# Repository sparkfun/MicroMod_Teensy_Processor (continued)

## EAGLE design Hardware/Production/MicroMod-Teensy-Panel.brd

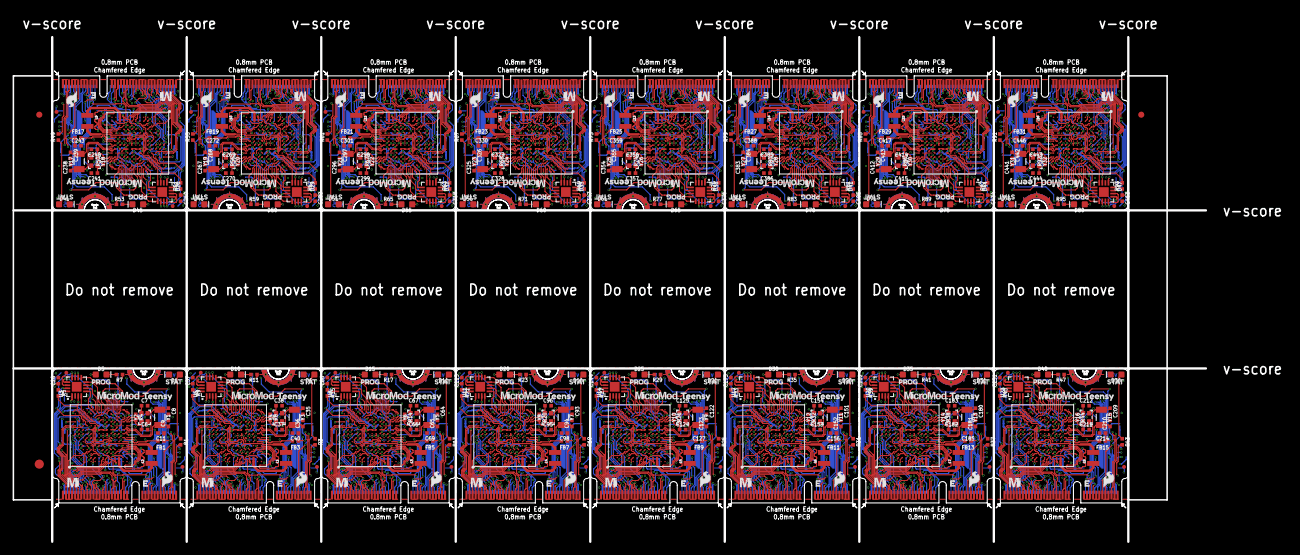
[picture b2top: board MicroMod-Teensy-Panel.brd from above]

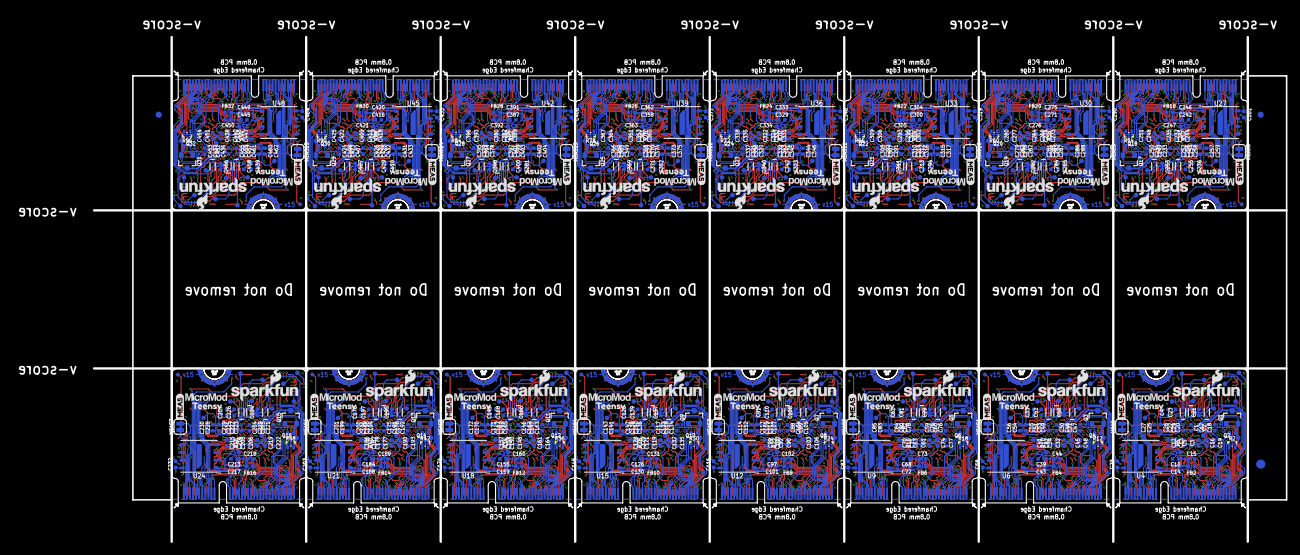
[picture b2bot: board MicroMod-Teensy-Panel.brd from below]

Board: 4 copper layers, 195.0 x 82.5 mm, 1270 parts (835 on the bottom side), 1520 nets.

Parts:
C1, C11, C30, C40, C59, C69, C88, C98, C117, C127, C146, C156, C175, C185, C204, C214, C233, C243, C262, C272, C291, C301, C320, C330, C349, C359, C378, C388, C407, C417, C436, C446: 2.2uF; 0402-TIGHT
C2, C14, C18, C26, C27, C31, C43, C47, C55, C56, C60, C72, C76, C84, C85, C89, C101, C105, C113, C114, C118, C130, C134, C142, C143, C147, C159, C163, C171, C172, C176, C188, C192, C200, C201, C205, C217, C221, C229, C230, C234, C246, C250, C258, C259, C263, C275, C279, C287, C288, C292, C304, C308, C316, C317, C321, C333, C337, C345, C346, C350, C362, C366, C374, C375, C379, C391, C395, C403, C404, C408, C420, C424, C432, C433, C437, C449, C453, C461, C462: 4.7uF; 0402-TIGHT
C3, C4, C12, C13, C15, C17, C20, C22, C23, C24, C25, C28, C29, C32, C33, C41, C42, C44, C46, C49, C51, C52, C53, C54, C57, C58, C61, C62, C70, C71, C73, C75, C78, C80, C81, C82, C83, C86, C87, C90, C91, C99, C100, C102, C104, C107, C109, C110, C111, C112, C115, C116, C119, C120, C128, C129, C131, C133, C136, C138, C139, C140, C141, C144, C145, C148, C149, C157, C158, C160, C162, C165, C167, C168, C169, C170, C173, C174, C177, C178, C186, C187, C189, C191, C194, C196, C197, C198, C199, C202, C203, C206, C207, C215, C216, C218, C220, C223, C225, C226, C227, C228, C231, C232, C235, C236, C244, C245, C247, C249, C252, C254, C255, C256, C257, C260, C261, C264, C265, C273, C274, C276, C278, C281, C283, C284, C285, C286, C289, C290, C293, C294, C302, C303, C305, C307, C310, C312, C313, C314, C315, C318, C319, C322, C323, C331, C332, C334, C336, C339, C341, C342, C343, C344, C347, C348, C351, C352, C360, C361, C363, C365, C368, C370, C371, C372, C373, C376, C377, C380, C381, C389, C390, C392, C394, C397, C399, C400, C401, C402, C405, C406, C409, C410, C418, C419, C421, C423, C426, C428, C429, C430, C431, C434, C435, C438, C439, C447, C448, C450, C452, C455, C457, C458, C459, C460, C463, C464: 0.22uF; 0402-TIGHT
C5, C16, C34, C45, C63, C74, C92, C103, C121, C132, C150, C161, C179, C190, C208, C219, C237, C248, C266, C277, C295, C306, C324, C335, C353, C364, C382, C393, C411, C422, C440, C451: 10nF; 0402-TIGHT
C6, C7, C37, C38, C66, C67, C95, C96, C124, C125, C153, C154, C182, C183, C211, C212, C240, C241, C269, C270, C298, C299, C327, C328, C356, C357, C385, C386, C414, C415, C443, C444: 12pF; 0402-TIGHT
C8, C9, C35, C36, C64, C65, C93, C94, C122, C123, C151, C152, C180, C181, C209, C210, C238, C239, C267, C268, C296, C297, C325, C326, C354, C355, C383, C384, C412, C413, C441, C442: 20pF; 0402-TIGHT
C10, C19, C21, C39, C48, C50, C68, C77, C79, C97, C106, C108, C126, C135, C137, C155, C164, C166, C184, C193, C195, C213, C222, C224, C242, C251, C253, C271, C280, C282, C300, C309, C311, C329, C338, C340, C358, C367, C369, C387, C396, C398, C416, C425, C427, C445, C454, C456: 10uF; 0402-TIGHT
D1, D6, D11, D16, D21, D26, D31, D36, D41, D46, D51, D56, D61, D66, D71, D76: BLUE; LED-0603
D2, D3, D4, D7, D8, D9, D12, D13, D14, D17, D18, D19, D22, D23, D24, D27, D28, D29, D32, D33, D34, D37, D38, D39, D42, D43, D44, D47, D48, D49, D52, D53, D54, D57, D58, D59, D62, D63, D64, D67, D68, D69, D72, D73, D74, D77, D78, D79: 120mA/40V/370mV; SOD-523
D5, D10, D15, D20, D25, D30, D35, D40, D45, D50, D55, D60, D65, D70, D75, D80: Yellow; LED-0603
E$1, E$2, E$3, E$4: FIDUCIAL-1X2
E$5, E$6: FIDUCIAL-1.5X3
FB1, FB2, FB3, FB4, FB5, FB6, FB7, FB8, FB9, FB10, FB11, FB12, FB13, FB14, FB15, FB16, FB17, FB18, FB19, FB20, FB21, FB22, FB23, FB24, FB25, FB26, FB27, FB28, FB29, FB30, FB31, FB32: 120Ω; 0402-TIGHT
FD1, FD2, FD3, FD4, FD5, FD6, FD7, FD8, FD9, FD10, FD11, FD12, FD13, FD14, FD15, FD16, FD17, FD18, FD19, FD20, FD21, FD22, FD23, FD24, FD25, FD26, FD27, FD28, FD29, FD30, FD31, FD32, FD33, FD34, FD35, FD36, FD37, FD38, FD39, FD40, FD41, FD42, FD43, FD44, FD45, FD46, FD47, FD48, FD49, FD50, FD51, FD52, FD53, FD54, FD55, FD56, FD57, FD58, FD59, FD60, FD61, FD62, FD63, FD64: FIDUCIALUFIDUCIAL; FIDUCIAL-MICRO
J1, J2, J3, J4, J5, J6, J7, J8, J9, J10, J11, J12, J13, J14, J15, J16: MICROMOD-2222; M.2-CARD-E-22
L1, L2, L3, L4, L5, L6, L7, L8, L9, L10, L11, L12, L13, L14, L15, L16: 4.7μH; 1008(2520)
LOGO1, LOGO2, LOGO3, LOGO4, LOGO5, LOGO6, LOGO7, LOGO8, LOGO9, LOGO10, LOGO11, LOGO12, LOGO13, LOGO14, LOGO15, LOGO16: SFE_LOGO_NAME_FLAME.1_INCH; SFE_LOGO_NAME_FLAME_.1
MEAS, MEAS1, MEAS2, MEAS3, MEAS4, MEAS5, MEAS6, MEAS7, MEAS8, MEAS9, MEAS10, MEAS11, MEAS12, MEAS13, MEAS14, MEAS15: SMT-JUMPER_2_NC_TRACE_SILK
Q1, Q3, Q5, Q7, Q9, Q11, Q13, Q15, Q17, Q19, Q21, Q23, Q25, Q27, Q29, Q31: 20V/4.2A/52mΩ/1.4W; SOT23-3
Q2, Q4, Q6, Q8, Q10, Q12, Q14, Q16, Q18, Q20, Q22, Q24, Q26, Q28, Q30, Q32: 20V/0.2A/8MHz/1.2Ω/1Vth; SOT-416FL
R1, R3, R7, R11, R13, R17, R19, R23, R25, R29, R31, R35, R37, R41, R43, R47, R49, R53, R55, R59, R61, R65, R67, R71, R73, R77, R79, R83, R85, R89, R91, R95: 1k; 0402-TIGHT
R2, R5, R6, R9, R10, R12, R15, R16, R18, R21, R22, R24, R27, R28, R30, R33, R34, R36, R39, R40, R42, R45, R46, R48, R51, R52, R54, R57, R58, R60, R63, R64, R66, R69, R70, R72, R75, R76, R78, R81, R82, R84, R87, R88, R90, R93, R94, R96: 100k; 0402-TIGHT
R4, R8, R14, R20, R26, R32, R38, R44, R50, R56, R62, R68, R74, R80, R86, R92: 2.2M; 0402-TIGHT
TP1, TP2, TP3, TP4, TP5, TP6, TP7, TP8, TP9, TP10, TP11, TP12, TP13, TP14, TP15, TP16, TP17, TP18, TP19, TP20, TP21, TP22, TP23, TP24, TP25, TP26, TP27, TP28, TP29, TP30, TP31, TP32, TP33, TP34, TP35, TP36, TP37, TP38, TP39, TP40, TP41, TP42, TP43, TP44, TP45, TP46, TP47, TP48, TP49, TP50, TP51, TP52, TP53, TP54, TP55, TP56, TP57, TP58, TP59, TP60, TP61, TP62, TP63, TP64, TP65, TP66, TP67, TP68, TP69, TP70, TP71, TP72, TP73, TP74, TP75, TP76, TP77, TP78, TP79, TP80, TP81, TP82, TP83, TP84, TP85, TP86, TP87, TP88, TP89, TP90, TP91, TP92, TP93, TP94, TP95, TP96, TP97, TP98, TP99, TP100, TP101, TP102, TP103, TP104, TP105, TP106, TP107, TP108, TP109, TP110, TP111, TP112, TP113, TP114, TP115, TP116, TP117, TP118, TP119, TP120, TP121, TP122, TP123, TP124, TP125, TP126, TP127, TP128, TP129, TP130, TP131, TP132, TP133, TP134, TP135, TP136, TP137, TP138, TP139, TP140, TP141, TP142, TP143, TP144, TP145, TP146, TP147, TP148, TP149, TP150, TP151, TP152, TP153, TP154, TP155, TP156, TP157, TP158, TP159, TP160, TP161, TP162, TP163, TP164, TP165, TP166, TP167, TP168, TP169, TP170, TP171, TP172, TP173, TP174, TP175, TP176, TP177, TP178, TP179, TP180, TP181, TP182, TP183, TP184, TP185, TP186, TP187, TP188, TP189, TP190, TP191, TP192, TP193, TP194, TP195, TP196, TP197, TP198, TP199, TP200, TP201, TP202, TP203, TP204, TP205, TP206, TP207, TP208: PAD.03X.03
U1, U2, U7, U10, U13, U16, U19, U22, U25, U28, U31, U34, U37, U40, U43, U46: IMXRT1062DV10X10; IMXRT1062
U3, U5, U8, U11, U14, U17, U20, U23, U26, U29, U32, U35, U38, U41, U44, U47: MKL02Z32VFG4; QFN-16
U4, U6, U9, U12, U15, U18, U21, U24, U27, U30, U33, U36, U39, U42, U45, U48: W25QXX128MBIT-6X5; WSON-8-6X5-SKINNY_CENTERPAD
U$1, U$2, U$3, U$5, U$19, U$20, U$28, U$29, U$37, U$38, U$46, U$47, U$55, U$56, U$64, U$65, U$73, U$74, U$82, U$83, U$91, U$92, U$100, U$101, U$109, U$110, U$118, U$119, U$127, U$128, U$136, U$137: TEENSY2
U$4, U$15, U$24, U$33, U$42, U$51, U$60, U$69, U$78, U$87, U$96, U$105, U$114, U$123, U$132, U$141: MICROMOD_MI_LOGO_.35
U$6, U$16, U$25, U$34, U$43, U$52, U$61, U$70, U$79, U$88, U$97, U$106, U$115, U$124, U$133, U$142: SFE_LOGO_FLAME_.1
U$7, U$11, U$17, U$18, U$26, U$27, U$35, U$36, U$44, U$45, U$53, U$54, U$62, U$63, U$71, U$72, U$80, U$81, U$89, U$90, U$98, U$99, U$107, U$108, U$116, U$117, U$125, U$126, U$134, U$135, U$143, U$144: MICROMOD_LOGO_.3
U$8, U$12, U$21, U$30, U$39, U$48, U$57, U$66, U$75, U$84, U$93, U$102, U$111, U$120, U$129, U$138: MEAS2
U$9, U$13, U$22, U$31, U$40, U$49, U$58, U$67, U$76, U$85, U$94, U$103, U$112, U$121, U$130, U$139: PROG0
U$10, U$14, U$23, U$32, U$41, U$50, U$59, U$68, U$77, U$86, U$95, U$104, U$113, U$122, U$131, U$140: STAT1
Y1, Y3, Y5, Y7, Y9, Y11, Y13, Y15, Y17, Y19, Y21, Y23, Y25, Y27, Y29, Y31: 32.768kHz; CRYSTAL-SMD-3.2X1.5MM
Y2, Y4, Y6, Y8, Y10, Y12, Y14, Y16, Y18, Y20, Y22, Y24, Y26, Y28, Y30, Y32: 24MHz; CRYSTAL-SMD-2.0X1.6MM

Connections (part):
3.3V: D2.A, J1.2, J1.74, Q1.2, R2.1, TP13.P$1
3.3V1: D7.A, J2.2, J2.74, Q3.2, R12.1, TP26.P$1
3.3V2: D12.A, J3.2, J3.74, Q5.2, R18.1, TP39.P$1
3.3V3: D17.A, J4.2, J4.74, Q7.2, R24.1, TP52.P$1
3.3V4: D22.A, J5.2, J5.74, Q9.2, R30.1, TP65.P$1
3.3V5: D27.A, J6.2, J6.74, Q11.2, R36.1, TP78.P$1
3.3V6: D32.A, J7.2, J7.74, Q13.2, R42.1, TP91.P$1
3.3V7: D37.A, J8.2, J8.74, Q15.2, R48.1, TP104.P$1
3.3V8: D42.A, J9.2, J9.74, Q17.2, R54.1, TP117.P$1
3.3V9: D47.A, J10.2, J10.74, Q19.2, R60.1, TP130.P$1
3.3V10: D52.A, J11.2, J11.74, Q21.2, R66.1, TP143.P$1
3.3V11: D57.A, J12.2, J12.74, Q23.2, R72.1, TP156.P$1
3.3V12: D62.A, J13.2, J13.74, Q25.2, R78.1, TP169.P$1
3.3V13: D67.A, J14.2, J14.74, Q27.2, R84.1, TP182.P$1
3.3V14: D72.A, J15.2, J15.74, Q29.2, R90.1, TP195.P$1
3.3V15: D77.A, J16.2, J16.74, Q31.2, R96.1, TP208.P$1
3.3V_CONTROLLED: C1.1, C2.1, C3.1, C4.1, C5.1, C28.1, C29.1, D5.A, FB2.1, Q1.3, R6.1, TP12.P$1, U1.E6, U1.E9, U1.F5, U1.F10, U1.J6, U1.J10, U1.K4, U1.K5, U1.N14, U1.P12, U3.1, U4.8
3.3V_CONTROLLED1: C30.1, C31.1, C32.1, C33.1, C34.1, C57.1, C58.1, D10.A, FB4.1, Q3.3, R10.1, TP25.P$1, U2.E6, U2.E9, U2.F5, U2.F10, U2.J6, U2.J10, U2.K4, U2.K5, U2.N14, U2.P12, U5.1, U6.8
3.3V_CONTROLLED2: C59.1, C60.1, C61.1, C62.1, C63.1, C86.1, C87.1, D15.A, FB6.1, Q5.3, R16.1, TP38.P$1, U7.E6, U7.E9, U7.F5, U7.F10, U7.J6, U7.J10, U7.K4, U7.K5, U7.N14, U7.P12, U8.1, U9.8
3.3V_CONTROLLED3: C88.1, C89.1, C90.1, C91.1, C92.1, C115.1, C116.1, D20.A, FB8.1, Q7.3, R22.1, TP51.P$1, U10.E6, U10.E9, U10.F5, U10.F10, U10.J6, U10.J10, U10.K4, U10.K5, U10.N14, U10.P12, U11.1, U12.8
3.3V_CONTROLLED4: C117.1, C118.1, C119.1, C120.1, C121.1, C144.1, C145.1, D25.A, FB10.1, Q9.3, R28.1, TP64.P$1, U13.E6, U13.E9, U13.F5, U13.F10, U13.J6, U13.J10, U13.K4, U13.K5, U13.N14, U13.P12, U14.1, U15.8
3.3V_CONTROLLED5: C146.1, C147.1, C148.1, C149.1, C150.1, C173.1, C174.1, D30.A, FB12.1, Q11.3, R34.1, TP77.P$1, U16.E6, U16.E9, U16.F5, U16.F10, U16.J6, U16.J10, U16.K4, U16.K5, U16.N14, U16.P12, U17.1, U18.8
3.3V_CONTROLLED6: C175.1, C176.1, C177.1, C178.1, C179.1, C202.1, C203.1, D35.A, FB14.1, Q13.3, R40.1, TP90.P$1, U19.E6, U19.E9, U19.F5, U19.F10, U19.J6, U19.J10, U19.K4, U19.K5, U19.N14, U19.P12, U20.1, U21.8
3.3V_CONTROLLED7: C204.1, C205.1, C206.1, C207.1, C208.1, C231.1, C232.1, D40.A, FB16.1, Q15.3, R46.1, TP103.P$1, U22.E6, U22.E9, U22.F5, U22.F10, U22.J6, U22.J10, U22.K4, U22.K5, U22.N14, U22.P12, U23.1, U24.8
3.3V_CONTROLLED8: C233.1, C234.1, C235.1, C236.1, C237.1, C260.1, C261.1, D45.A, FB18.1, Q17.3, R52.1, TP116.P$1, U25.E6, U25.E9, U25.F5, U25.F10, U25.J6, U25.J10, U25.K4, U25.K5, U25.N14, U25.P12, U26.1, U27.8
3.3V_CONTROLLED9: C262.1, C263.1, C264.1, C265.1, C266.1, C289.1, C290.1, D50.A, FB20.1, Q19.3, R58.1, TP129.P$1, U28.E6, U28.E9, U28.F5, U28.F10, U28.J6, U28.J10, U28.K4, U28.K5, U28.N14, U28.P12, U29.1, U30.8
3.3V_CONTROLLED10: C291.1, C292.1, C293.1, C294.1, C295.1, C318.1, C319.1, D55.A, FB22.1, Q21.3, R64.1, TP142.P$1, U31.E6, U31.E9, U31.F5, U31.F10, U31.J6, U31.J10, U31.K4, U31.K5, U31.N14, U31.P12, U32.1, U33.8
3.3V_CONTROLLED11: C320.1, C321.1, C322.1, C323.1, C324.1, C347.1, C348.1, D60.A, FB24.1, Q23.3, R70.1, TP155.P$1, U34.E6, U34.E9, U34.F5, U34.F10, U34.J6, U34.J10, U34.K4, U34.K5, U34.N14, U34.P12, U35.1, U36.8
3.3V_CONTROLLED12: C349.1, C350.1, C351.1, C352.1, C353.1, C376.1, C377.1, D65.A, FB26.1, Q25.3, R76.1, TP168.P$1, U37.E6, U37.E9, U37.F5, U37.F10, U37.J6, U37.J10, U37.K4, U37.K5, U37.N14, U37.P12, U38.1, U39.8
3.3V_CONTROLLED13: C378.1, C379.1, C380.1, C381.1, C382.1, C405.1, C406.1, D70.A, FB28.1, Q27.3, R82.1, TP181.P$1, U40.E6, U40.E9, U40.F5, U40.F10, U40.J6, U40.J10, U40.K4, U40.K5, U40.N14, U40.P12, U41.1, U42.8
3.3V_CONTROLLED14: C407.1, C408.1, C409.1, C410.1, C411.1, C434.1, C435.1, D75.A, FB30.1, Q29.3, R88.1, TP194.P$1, U43.E6, U43.E9, U43.F5, U43.F10, U43.J6, U43.J10, U43.K4, U43.K5, U43.N14, U43.P12, U44.1, U45.8
3.3V_CONTROLLED15: C436.1, C437.1, C438.1, C439.1, C440.1, C463.1, C464.1, D80.A, FB32.1, Q31.3, R94.1, TP207.P$1, U46.E6, U46.E9, U46.F5, U46.F10, U46.J6, U46.J10, U46.K4, U46.K5, U46.N14, U46.P12, U47.1, U48.8
24MHZ_1: C7.1, U1.N11, Y2.3
24MHZ_2: C6.1, R4.2, U1.P11, Y2.1
24MHZ_3: C38.1, U2.N11, Y4.3
24MHZ_4: C37.1, R8.2, U2.P11, Y4.1
24MHZ_5: C67.1, U7.N11, Y6.3
24MHZ_6: C66.1, R14.2, U7.P11, Y6.1
24MHZ_7: C96.1, U10.N11, Y8.3
24MHZ_8: C95.1, R20.2, U10.P11, Y8.1
24MHZ_9: C125.1, U13.N11, Y10.3
24MHZ_10: C124.1, R26.2, U13.P11, Y10.1
24MHZ_11: C154.1, U16.N11, Y12.3
24MHZ_12: C153.1, R32.2, U16.P11, Y12.1
24MHZ_13: C183.1, U19.N11, Y14.3
24MHZ_14: C182.1, R38.2, U19.P11, Y14.1
24MHZ_15: C212.1, U22.N11, Y16.3
24MHZ_16: C211.1, R44.2, U22.P11, Y16.1
24MHZ_17: C241.1, U25.N11, Y18.3
24MHZ_18: C240.1, R50.2, U25.P11, Y18.1
24MHZ_19: C270.1, U28.N11, Y20.3
24MHZ_20: C269.1, R56.2, U28.P11, Y20.1
24MHZ_21: C299.1, U31.N11, Y22.3
24MHZ_22: C298.1, R62.2, U31.P11, Y22.1
24MHZ_23: C328.1, U34.N11, Y24.3
24MHZ_24: C327.1, R68.2, U34.P11, Y24.1
24MHZ_25: C357.1, U37.N11, Y26.3
24MHZ_26: C356.1, R74.2, U37.P11, Y26.1
24MHZ_27: C386.1, U40.N11, Y28.3
24MHZ_28: C385.1, R80.2, U40.P11, Y28.1
24MHZ_29: C415.1, U43.N11, Y30.3
24MHZ_30: C414.1, R86.2, U43.P11, Y30.1
24MHZ_31: C444.1, U46.N11, Y32.3
24MHZ_32: C443.1, R92.2, U46.P11, Y32.1
32KHZ_1: C8.1, U1.N9, Y1.P$1
32KHZ_2: C9.1, U1.P9, Y1.P$2
32KHZ_3: C36.1, U2.P9, Y3.P$2
32KHZ_4: C35.1, U2.N9, Y3.P$1
32KHZ_5: C65.1, U7.P9, Y5.P$2
32KHZ_6: C64.1, U7.N9, Y5.P$1
32KHZ_7: C94.1, U10.P9, Y7.P$2
32KHZ_8: C93.1, U10.N9, Y7.P$1
32KHZ_9: C123.1, U13.P9, Y9.P$2
32KHZ_10: C122.1, U13.N9, Y9.P$1
32KHZ_11: C152.1, U16.P9, Y11.P$2
32KHZ_12: C151.1, U16.N9, Y11.P$1
32KHZ_13: C181.1, U19.P9, Y13.P$2
32KHZ_14: C180.1, U19.N9, Y13.P$1
32KHZ_15: C210.1, U22.P9, Y15.P$2
32KHZ_16: C209.1, U22.N9, Y15.P$1
32KHZ_17: C239.1, U25.P9, Y17.P$2
32KHZ_18: C238.1, U25.N9, Y17.P$1
32KHZ_19: C268.1, U28.P9, Y19.P$2
32KHZ_20: C267.1, U28.N9, Y19.P$1
32KHZ_21: C297.1, U31.P9, Y21.P$2
32KHZ_22: C296.1, U31.N9, Y21.P$1
32KHZ_23: C326.1, U34.P9, Y23.P$2
32KHZ_24: C325.1, U34.N9, Y23.P$1
32KHZ_25: C355.1, U37.P9, Y25.P$2
32KHZ_26: C354.1, U37.N9, Y25.P$1
32KHZ_27: C384.1, U40.P9, Y27.P$2
32KHZ_28: C383.1, U40.N9, Y27.P$1
32KHZ_29: C413.1, U43.P9, Y29.P$2
32KHZ_30: C412.1, U43.N9, Y29.P$1
32KHZ_31: C442.1, U46.P9, Y31.P$2
32KHZ_32: C441.1, U46.N9, Y31.P$1
32KHZ_TEST: TP1.P$1, U1.M14
32KHZ_TEST1: TP14.P$1, U2.M14
32KHZ_TEST2: TP27.P$1, U7.M14
32KHZ_TEST3: TP40.P$1, U10.M14
32KHZ_TEST4: TP53.P$1, U13.M14
32KHZ_TEST5: TP66.P$1, U16.M14
32KHZ_TEST6: TP79.P$1, U19.M14
32KHZ_TEST7: TP92.P$1, U22.M14
32KHZ_TEST8: TP105.P$1, U25.M14
32KHZ_TEST9: TP118.P$1, U28.M14
32KHZ_TEST10: TP131.P$1, U31.M14
32KHZ_TEST11: TP144.P$1, U34.M14
32KHZ_TEST12: TP157.P$1, U37.M14
32KHZ_TEST13: TP170.P$1, U40.M14
32KHZ_TEST14: TP183.P$1, U43.M14
32KHZ_TEST15: TP196.P$1, U46.M14
34/DAT1: J1.66, U1.K1
34/DAT2: J2.66, U2.K1
34/DAT3: J3.66, U7.K1
34/DAT4: J4.66, U10.K1
34/DAT5: J5.66, U13.K1
34/DAT6: J6.66, U16.K1
34/DAT7: J7.66, U19.K1
34/DAT8: J8.66, U22.K1
34/DAT9: J9.66, U25.K1
34/DAT10: J10.66, U28.K1
34/DAT11: J11.66, U31.K1
34/DAT12: J12.66, U34.K1
34/DAT13: J13.66, U37.K1
34/DAT14: J14.66, U40.K1
34/DAT15: J15.66, U43.K1
34/DAT16: J16.66, U46.K1
35/DAT0: J1.64, U1.J1
35/DAT1: J2.64, U2.J1
35/DAT2: J3.64, U7.J1
35/DAT3: J4.64, U10.J1
35/DAT4: J5.64, U13.J1
35/DAT5: J6.64, U16.J1
35/DAT6: J7.64, U19.J1
35/DAT7: J8.64, U22.J1
35/DAT8: J9.64, U25.J1
35/DAT9: J10.64, U28.J1
35/DAT10: J11.64, U31.J1
35/DAT11: J12.64, U34.J1
35/DAT12: J13.64, U37.J1
35/DAT13: J14.64, U40.J1
35/DAT14: J15.64, U43.J1
35/DAT15: J16.64, U46.J1
36/CLK: J1.60, U1.J3
36/CLK1: J2.60, U2.J3
36/CLK2: J3.60, U7.J3
36/CLK3: J4.60, U10.J3
36/CLK4: J5.60, U13.J3
36/CLK5: J6.60, U16.J3
36/CLK6: J7.60, U19.J3
36/CLK7: J8.60, U22.J3
36/CLK8: J9.60, U25.J3
36/CLK9: J10.60, U28.J3
36/CLK10: J11.60, U31.J3
36/CLK11: J12.60, U34.J3
36/CLK12: J13.60, U37.J3
36/CLK13: J14.60, U40.J3
36/CLK14: J15.60, U43.J3
36/CLK15: J16.60, U46.J3
37/CMD: J1.62, U1.J4
37/CMD1: J2.62, U2.J4
37/CMD2: J3.62, U7.J4
37/CMD3: J4.62, U10.J4
37/CMD4: J5.62, U13.J4
37/CMD5: J6.62, U16.J4
37/CMD6: J7.62, U19.J4
37/CMD7: J8.62, U22.J4
37/CMD8: J9.62, U25.J4
37/CMD9: J10.62, U28.J4
37/CMD10: J11.62, U31.J4
37/CMD11: J12.62, U34.J4
37/CMD12: J13.62, U37.J4
37/CMD13: J14.62, U40.J4
37/CMD14: J15.62, U43.J4
37/CMD15: J16.62, U46.J4
38/DAT1: J2.68, U2.H2
38/DAT2: J1.68, U1.H2
38/DAT3: J3.68, U7.H2
38/DAT4: J4.68, U10.H2
38/DAT5: J5.68, U13.H2
38/DAT6: J6.68, U16.H2
38/DAT7: J7.68, U19.H2
38/DAT8: J8.68, U22.H2
38/DAT9: J9.68, U25.H2
38/DAT10: J10.68, U28.H2
38/DAT11: J11.68, U31.H2
38/DAT12: J12.68, U34.H2
38/DAT13: J13.68, U37.H2
38/DAT14: J14.68, U40.H2
38/DAT15: J15.68, U43.H2
38/DAT16: J16.68, U46.H2
39/DAT1: J2.70, U2.J2
39/DAT2: J3.70, U7.J2
39/DAT3: J1.70, U1.J2
39/DAT4: J4.70, U10.J2
39/DAT5: J5.70, U13.J2
39/DAT6: J6.70, U16.J2
39/DAT7: J7.70, U19.J2
39/DAT8: J8.70, U22.J2
39/DAT9: J9.70, U25.J2
39/DAT10: J10.70, U28.J2
39/DAT11: J11.70, U31.J2
39/DAT12: J12.70, U34.J2
39/DAT13: J13.70, U37.J2
39/DAT14: J14.70, U40.J2
39/DAT15: J15.70, U43.J2
39/DAT16: J16.70, U46.J2
A0/1: J2.34, U2.L11
A0/2: J3.34, U7.L11
A0/3: J4.34, U10.L11
A0/4: J5.34, U13.L11
A0/5: J6.34, U16.L11
A0/6: J7.34, U19.L11
A0/7: J8.34, U22.L11
A0/8: J9.34, U25.L11
A0/9: J10.34, U28.L11
A0/10: J11.34, U31.L11
A0/11: J12.34, U34.L11
A0/12: J13.34, U37.L11
A0/13: J14.34, U40.L11
A0/14: J1.34, U1.L11
A0/15: J15.34, U43.L11
A0/16: J16.34, U46.L11
A1/1: J2.38, U2.M12
A1/2: J3.38, U7.M12
A1/3: J4.38, U10.M12
A1/4: J5.38, U13.M12
A1/5: J6.38, U16.M12
A1/6: J7.38, U19.M12
A1/7: J8.38, U22.M12
A1/8: J9.38, U25.M12
A1/9: J10.38, U28.M12
A1/10: J11.38, U31.M12
A1/11: J12.38, U34.M12
A1/12: J13.38, U37.M12
A1/13: J14.38, U40.M12
A1/14: J15.38, U43.M12
A1/15: J1.38, U1.M12
A1/16: J16.38, U46.M12
AUD_IN/1: J2.54, U2.A11
AUD_IN/2: J3.54, U7.A11
AUD_IN/3: J4.54, U10.A11
AUD_IN/4: J5.54, U13.A11
AUD_IN/5: J6.54, U16.A11
AUD_IN/6: J7.54, U19.A11
AUD_IN/7: J8.54, U22.A11
AUD_IN/8: J1.54, U1.A11
AUD_IN/9: J9.54, U25.A11
AUD_IN/10: J10.54, U28.A11
AUD_IN/11: J11.54, U31.A11
AUD_IN/12: J12.54, U34.A11
AUD_IN/13: J13.54, U37.A11
AUD_IN/14: J14.54, U40.A11
AUD_IN/15: J15.54, U43.A11
AUD_IN/16: J16.54, U46.A11
AUD_OUT/1: J2.56, U2.B11
AUD_OUT/2: J3.56, U7.B11
AUD_OUT/3: J4.56, U10.B11
AUD_OUT/4: J5.56, U13.B11
AUD_OUT/5: J6.56, U16.B11
AUD_OUT/6: J7.56, U19.B11
AUD_OUT/7: J1.56, U1.B11
AUD_OUT/8: J8.56, U22.B11
AUD_OUT/9: J9.56, U25.B11
AUD_OUT/10: J10.56, U28.B11
AUD_OUT/11: J11.56, U31.B11
AUD_OUT/12: J12.56, U34.B11
AUD_OUT/13: J13.56, U37.B11
AUD_OUT/14: J14.56, U40.B11
AUD_OUT/15: J15.56, U43.B11
AUD_OUT/16: J16.56, U46.B11
BATT_VIN/22/A1: J2.49, U2.H13
BATT_VIN/22/A2: J3.49, U7.H13
BATT_VIN/22/A3: J4.49, U10.H13
BATT_VIN/22/A4: J5.49, U13.H13
BATT_VIN/22/A5: J6.49, U16.H13
BATT_VIN/22/A6: J7.49, U19.H13
BATT_VIN/22/A7: J8.49, U22.H13
BATT_VIN/22/A8: J1.49, U1.H13
BATT_VIN/22/A9: J9.49, U25.H13
BATT_VIN/22/A10: J10.49, U28.H13
BATT_VIN/22/A11: J11.49, U31.H13
BATT_VIN/22/A12: J12.49, U34.H13
BATT_VIN/22/A13: J13.49, U37.H13
BATT_VIN/22/A14: J14.49, U40.H13
BATT_VIN/22/A15: J15.49, U43.H13
BATT_VIN/22/A16: J16.49, U46.H13
BCLK/21/A1: J2.50, U2.J13
BCLK/21/A2: J3.50, U7.J13
BCLK/21/A3: J4.50, U10.J13
BCLK/21/A4: J5.50, U13.J13
BCLK/21/A5: J6.50, U16.J13
BCLK/21/A6: J7.50, U19.J13
BCLK/21/A7: J1.50, U1.J13
BCLK/21/A8: J8.50, U22.J13
BCLK/21/A9: J9.50, U25.J13
BCLK/21/A10: J10.50, U28.J13
BCLK/21/A11: J11.50, U31.J13
BCLK/21/A12: J12.50, U34.J13
BCLK/21/A13: J13.50, U37.J13
BCLK/21/A14: J14.50, U40.J13
BCLK/21/A15: J15.50, U43.J13
BCLK/21/A16: J16.50, U46.J13
BOOTMODE0: U1.F11, U3.4
BOOTMODE1: U2.F11, U5.4
BOOTMODE2: U7.F11, U8.4
BOOTMODE3: U10.F11, U11.4
BOOTMODE4: U13.F11, U14.4
BOOTMODE5: U16.F11, U17.4
BOOTMODE6: U19.F11, U20.4
BOOTMODE7: U22.F11, U23.4
BOOTMODE8: U25.F11, U26.4
BOOTMODE9: U28.F11, U29.4
BOOTMODE10: U31.F11, U32.4
BOOTMODE11: U34.F11, U35.4
BOOTMODE12: U37.F11, U38.4
BOOTMODE13: U40.F11, U41.4
BOOTMODE14: U43.F11, U44.4
BOOTMODE15: U46.F11, U47.4
CAN_RX/1: J2.41, U2.E4
CAN_RX/2: J3.41, U7.E4
CAN_RX/3: J4.41, U10.E4
CAN_RX/4: J5.41, U13.E4
CAN_RX/5: J6.41, U16.E4
CAN_RX/6: J7.41, U19.E4
CAN_RX/7: J8.41, U22.E4
CAN_RX/8: J9.41, U25.E4
CAN_RX/9: J10.41, U28.E4
CAN_RX/10: J11.41, U31.E4
CAN_RX/11: J12.41, U34.E4
CAN_RX/12: J13.41, U37.E4
CAN_RX/13: J14.41, U40.E4
CAN_RX/14: J15.41, U43.E4
CAN_RX/15: J16.41, U46.E4
CAN_RX/30: J1.41, U1.E4
CAN_TX/1: J2.43, U2.C3
CAN_TX/2: J3.43, U7.C3
CAN_TX/3: J4.43, U10.C3
CAN_TX/4: J5.43, U13.C3
CAN_TX/5: J6.43, U16.C3
CAN_TX/6: J7.43, U19.C3
CAN_TX/7: J8.43, U22.C3
CAN_TX/8: J9.43, U25.C3
CAN_TX/9: J10.43, U28.C3
CAN_TX/10: J11.43, U31.C3
CAN_TX/11: J12.43, U34.C3
CAN_TX/12: J13.43, U37.C3
CAN_TX/13: J14.43, U40.C3
CAN_TX/14: J15.43, U43.C3
CAN_TX/15: J16.43, U46.C3
CAN_TX/31: J1.43, U1.C3
CIPO/1: J2.61, U2.E7
CIPO/2: J3.61, U7.E7
CIPO/3: J4.61, U10.E7
CIPO/4: J5.61, U13.E7
CIPO/5: J6.61, U16.E7
CIPO/6: J7.61, U19.E7
CIPO/7: J8.61, U22.E7
CIPO/8: J9.61, U25.E7
CIPO/9: J10.61, U28.E7
CIPO/10: J11.61, U31.E7
CIPO/11: J12.61, U34.E7
CIPO/12: J1.61, U1.E7
CIPO/13: J13.61, U37.E7
CIPO/14: J14.61, U40.E7
CIPO/15: J15.61, U43.E7
CIPO/16: J16.61, U46.E7
COPI/1: J2.59, U2.E8
COPI/2: J3.59, U7.E8
COPI/3: J4.59, U10.E8
COPI/4: J5.59, U13.E8
COPI/5: J6.59, U16.E8
COPI/6: J7.59, U19.E8
COPI/7: J8.59, U22.E8
COPI/8: J9.59, U25.E8
COPI/9: J10.59, U28.E8
COPI/10: J11.59, U31.E8
COPI/11: J1.59, U1.E8
COPI/12: J12.59, U34.E8
COPI/13: J13.59, U37.E8
COPI/14: J14.59, U40.E8
COPI/15: J15.59, U43.E8
COPI/16: J16.59, U46.E8
CS/1: J2.55, U2.D7
CS/2: J3.55, U7.D7
CS/3: J4.55, U10.D7
CS/4: J5.55, U13.D7
CS/5: J6.55, U16.D7
CS/6: J7.55, U19.D7
CS/7: J8.55, U22.D7
CS/8: J9.55, U25.D7
CS/9: J10.55, U28.D7
CS/10: J1.55, U1.D7
CS/11: J11.55, U31.D7
CS/12: J12.55, U34.D7
CS/13: J13.55, U37.D7
CS/14: J14.55, U40.D7
CS/15: J15.55, U43.D7
CS/16: J16.55, U46.D7
D0/1: J2.10, U2.H5
D0/2: J3.10, U7.H5
D0/3: J4.10, U10.H5
D0/4: J1.10, U1.H5
D0/5: J5.10, U13.H5
D0/6: J6.10, U16.H5
D0/7: J7.10, U19.H5
D0/8: J8.10, U22.H5
D0/9: J9.10, U25.H5
D0/10: J10.10, U28.H5
D0/11: J11.10, U31.H5
D0/12: J12.10, U34.H5
D0/13: J13.10, U37.H5
D0/14: J14.10, U40.H5
D0/15: J15.10, U43.H5
D0/16: J16.10, U46.H5
D1/1: J2.18, U2.H3
D1/2: J3.18, U7.H3
D1/3: J4.18, U10.H3
D1/4: J5.18, U13.H3
D1/5: J1.18, U1.H3
D1/6: J6.18, U16.H3
D1/7: J7.18, U19.H3
D1/8: J8.18, U22.H3
D1/9: J9.18, U25.H3
D1/10: J10.18, U28.H3
D1/11: J11.18, U31.H3
D1/12: J12.18, U34.H3
D1/13: J13.18, U37.H3
D1/14: J14.18, U40.H3
D1/15: J15.18, U43.H3
D1/16: J16.18, U46.H3
DCDC_IN: C10.1, C14.1, C15.1, FB2.2, U1.L1, U1.L2
DCDC_IN1: C39.1, C43.1, C44.1, FB4.2, U2.L1, U2.L2
DCDC_IN2: C68.1, C72.1, C73.1, FB6.2, U7.L1, U7.L2
DCDC_IN3: C97.1, C101.1, C102.1, FB8.2, U10.L1, U10.L2
DCDC_IN4: C126.1, C130.1, C131.1, FB10.2, U13.L1, U13.L2
DCDC_IN5: C155.1, C159.1, C160.1, FB12.2, U16.L1, U16.L2
DCDC_IN6: C184.1, C188.1, C189.1, FB14.2, U19.L1, U19.L2
DCDC_IN7: C213.1, C217.1, C218.1, FB16.2, U22.L1, U22.L2
DCDC_IN8: C242.1, C246.1, C247.1, FB18.2, U25.L1, U25.L2
DCDC_IN9: C271.1, C275.1, C276.1, FB20.2, U28.L1, U28.L2
DCDC_IN10: C300.1, C304.1, C305.1, FB22.2, U31.L1, U31.L2
DCDC_IN11: C329.1, C333.1, C334.1, FB24.2, U34.L1, U34.L2
DCDC_IN12: C358.1, C362.1, C363.1, FB26.2, U37.L1, U37.L2
DCDC_IN13: C387.1, C391.1, C392.1, FB28.2, U40.L1, U40.L2
DCDC_IN14: C416.1, C420.1, C421.1, FB30.2, U43.L1, U43.L2
DCDC_IN15: C445.1, C449.1, C450.1, FB32.2, U46.L1, U46.L2
DCDC_LP: L2.1, U1.M1, U1.M2
DCDC_LP1: L1.1, U2.M1, U2.M2
DCDC_LP2: L3.1, U7.M1, U7.M2
DCDC_LP3: L4.1, U10.M1, U10.M2
DCDC_LP4: L5.1, U13.M1, U13.M2
DCDC_LP5: L6.1, U16.M1, U16.M2
DCDC_LP6: L7.1, U19.M1, U19.M2
DCDC_LP7: L8.1, U22.M1, U22.M2
DCDC_LP8: L9.1, U25.M1, U25.M2
DCDC_LP9: L10.1, U28.M1, U28.M2
DCDC_LP10: L11.1, U31.M1, U31.M2
DCDC_LP11: L12.1, U34.M1, U34.M2
DCDC_LP12: L13.1, U37.M1, U37.M2
DCDC_LP13: L14.1, U40.M1, U40.M2
DCDC_LP14: L15.1, U43.M1, U43.M2
DCDC_LP15: L16.1, U46.M1, U46.M2
DEBUG_EN: U1.F3, U3.15
DEBUG_EN1: U2.F3, U5.15
DEBUG_EN2: U7.F3, U8.15
DEBUG_EN3: U10.F3, U11.15
DEBUG_EN4: U13.F3, U14.15
DEBUG_EN5: U16.F3, U17.15
DEBUG_EN6: U19.F3, U20.15
DEBUG_EN7: U22.F3, U23.15
DEBUG_EN8: U25.F3, U26.15
DEBUG_EN9: U28.F3, U29.15
DEBUG_EN10: U31.F3, U32.15
DEBUG_EN11: U34.F3, U35.15
DEBUG_EN12: U37.F3, U38.15
DEBUG_EN13: U40.F3, U41.15
DEBUG_EN14: U43.F3, U44.15
DEBUG_EN15: U46.F3, U47.15
DEBUG_SWO: U1.D10, U3.12
DEBUG_SWO1: U2.D10, U5.12
DEBUG_SWO2: U7.D10, U8.12
DEBUG_SWO3: U10.D10, U11.12
DEBUG_SWO4: U13.D10, U14.12
DEBUG_SWO5: U16.D10, U17.12
DEBUG_SWO6: U19.D10, U20.12
DEBUG_SWO7: U22.D10, U23.12
DEBUG_SWO8: U25.D10, U26.12
DEBUG_SWO9: U28.D10, U29.12
DEBUG_SWO10: U31.D10, U32.12
DEBUG_SWO11: U34.D10, U35.12
DEBUG_SWO12: U37.D10, U38.12
DEBUG_SWO13: U40.D10, U41.12
DEBUG_SWO14: U43.D10, U44.12
DEBUG_SWO15: U46.D10, U47.12
GND: C1.2, C2.2, C3.2, C4.2, C5.2, C6.2, C7.2, C8.2, C9.2, C10.2, C11.2, C12.2, C13.2, C14.2, C15.2, C16.2, C17.2, C18.2, C19.2, C20.2, C21.2, C22.2, C23.2, C24.2, C25.2, C26.2, C27.2, C28.2, C29.2, D1.C, J1.1, J1.7, J1.33, J1.36, J1.39, J1.45, J1.75, J1.GND1, J1.GND2, J1.GND3, Q2.2, R4.1, R5.1, U1.A1, U1.A14, U1.B5, U1.B10, U1.E2, U1.E13, U1.G7, U1.G8, U1.G14, U1.H7, U1.H8, U1.J7, U1.J8, U1.K2, U1.K6, U1.K9, U1.K13, U1.L9, U1.N1, U1.N2, U1.N5, U1.N8, U1.P1, U1.P14, U3.2, U3.17, U4.4
GND1: C30.2, C31.2, C32.2, C33.2, C34.2, C35.2, C36.2, C37.2, C38.2, C39.2, C40.2, C41.2, C42.2, C43.2, C44.2, C45.2, C46.2, C47.2, C48.2, C49.2, C50.2, C51.2, C52.2, C53.2, C54.2, C55.2, C56.2, C57.2, C58.2, D6.C, J2.1, J2.7, J2.33, J2.36, J2.39, J2.45, J2.75, J2.GND1, J2.GND2, J2.GND3, Q4.2, R8.1, R9.1, U2.A1, U2.A14, U2.B5, U2.B10, U2.E2, U2.E13, U2.G7, U2.G8, U2.G14, U2.H7, U2.H8, U2.J7, U2.J8, U2.K2, U2.K6, U2.K9, U2.K13, U2.L9, U2.N1, U2.N2, U2.N5, U2.N8, U2.P1, U2.P14, U5.2, U5.17, U6.4
GND2: C59.2, C60.2, C61.2, C62.2, C63.2, C64.2, C65.2, C66.2, C67.2, C68.2, C69.2, C70.2, C71.2, C72.2, C73.2, C74.2, C75.2, C76.2, C77.2, C78.2, C79.2, C80.2, C81.2, C82.2, C83.2, C84.2, C85.2, C86.2, C87.2, D11.C, J3.1, J3.7, J3.33, J3.36, J3.39, J3.45, J3.75, J3.GND1, J3.GND2, J3.GND3, Q6.2, R14.1, R15.1, U7.A1, U7.A14, U7.B5, U7.B10, U7.E2, U7.E13, U7.G7, U7.G8, U7.G14, U7.H7, U7.H8, U7.J7, U7.J8, U7.K2, U7.K6, U7.K9, U7.K13, U7.L9, U7.N1, U7.N2, U7.N5, U7.N8, U7.P1, U7.P14, U8.2, U8.17, U9.4
GND3: C88.2, C89.2, C90.2, C91.2, C92.2, C93.2, C94.2, C95.2, C96.2, C97.2, C98.2, C99.2, C100.2, C101.2, C102.2, C103.2, C104.2, C105.2, C106.2, C107.2, C108.2, C109.2, C110.2, C111.2, C112.2, C113.2, C114.2, C115.2, C116.2, D16.C, J4.1, J4.7, J4.33, J4.36, J4.39, J4.45, J4.75, J4.GND1, J4.GND2, J4.GND3, Q8.2, R20.1, R21.1, U10.A1, U10.A14, U10.B5, U10.B10, U10.E2, U10.E13, U10.G7, U10.G8, U10.G14, U10.H7, U10.H8, U10.J7, U10.J8, U10.K2, U10.K6, U10.K9, U10.K13, U10.L9, U10.N1, U10.N2, U10.N5, U10.N8, U10.P1, U10.P14, U11.2, U11.17, U12.4
GND4: C117.2, C118.2, C119.2, C120.2, C121.2, C122.2, C123.2, C124.2, C125.2, C126.2, C127.2, C128.2, C129.2, C130.2, C131.2, C132.2, C133.2, C134.2, C135.2, C136.2, C137.2, C138.2, C139.2, C140.2, C141.2, C142.2, C143.2, C144.2, C145.2, D21.C, J5.1, J5.7, J5.33, J5.36, J5.39, J5.45, J5.75, J5.GND1, J5.GND2, J5.GND3, Q10.2, R26.1, R27.1, U13.A1, U13.A14, U13.B5, U13.B10, U13.E2, U13.E13, U13.G7, U13.G8, U13.G14, U13.H7, U13.H8, U13.J7, U13.J8, U13.K2, U13.K6, U13.K9, U13.K13, U13.L9, U13.N1, U13.N2, U13.N5, U13.N8, U13.P1, U13.P14, U14.2, U14.17, U15.4
GND5: C146.2, C147.2, C148.2, C149.2, C150.2, C151.2, C152.2, C153.2, C154.2, C155.2, C156.2, C157.2, C158.2, C159.2, C160.2, C161.2, C162.2, C163.2, C164.2, C165.2, C166.2, C167.2, C168.2, C169.2, C170.2, C171.2, C172.2, C173.2, C174.2, D26.C, J6.1, J6.7, J6.33, J6.36, J6.39, J6.45, J6.75, J6.GND1, J6.GND2, J6.GND3, Q12.2, R32.1, R33.1, U16.A1, U16.A14, U16.B5, U16.B10, U16.E2, U16.E13, U16.G7, U16.G8, U16.G14, U16.H7, U16.H8, U16.J7, U16.J8, U16.K2, U16.K6, U16.K9, U16.K13, U16.L9, U16.N1, U16.N2, U16.N5, U16.N8, U16.P1, U16.P14, U17.2, U17.17, U18.4
GND6: C175.2, C176.2, C177.2, C178.2, C179.2, C180.2, C181.2, C182.2, C183.2, C184.2, C185.2, C186.2, C187.2, C188.2, C189.2, C190.2, C191.2, C192.2, C193.2, C194.2, C195.2, C196.2, C197.2, C198.2, C199.2, C200.2, C201.2, C202.2, C203.2, D31.C, J7.1, J7.7, J7.33, J7.36, J7.39, J7.45, J7.75, J7.GND1, J7.GND2, J7.GND3, Q14.2, R38.1, R39.1, U19.A1, U19.A14, U19.B5, U19.B10, U19.E2, U19.E13, U19.G7, U19.G8, U19.G14, U19.H7, U19.H8, U19.J7, U19.J8, U19.K2, U19.K6, U19.K9, U19.K13, U19.L9, U19.N1, U19.N2, U19.N5, U19.N8, U19.P1, U19.P14, U20.2, U20.17, U21.4
GND7: C204.2, C205.2, C206.2, C207.2, C208.2, C209.2, C210.2, C211.2, C212.2, C213.2, C214.2, C215.2, C216.2, C217.2, C218.2, C219.2, C220.2, C221.2, C222.2, C223.2, C224.2, C225.2, C226.2, C227.2, C228.2, C229.2, C230.2, C231.2, C232.2, D36.C, J8.1, J8.7, J8.33, J8.36, J8.39, J8.45, J8.75, J8.GND1, J8.GND2, J8.GND3, Q16.2, R44.1, R45.1, U22.A1, U22.A14, U22.B5, U22.B10, U22.E2, U22.E13, U22.G7, U22.G8, U22.G14, U22.H7, U22.H8, U22.J7, U22.J8, U22.K2, U22.K6, U22.K9, U22.K13, U22.L9, U22.N1, U22.N2, U22.N5, U22.N8, U22.P1, U22.P14, U23.2, U23.17, U24.4
GND8: C233.2, C234.2, C235.2, C236.2, C237.2, C238.2, C239.2, C240.2, C241.2, C242.2, C243.2, C244.2, C245.2, C246.2, C247.2, C248.2, C249.2, C250.2, C251.2, C252.2, C253.2, C254.2, C255.2, C256.2, C257.2, C258.2, C259.2, C260.2, C261.2, D41.C, J9.1, J9.7, J9.33, J9.36, J9.39, J9.45, J9.75, J9.GND1, J9.GND2, J9.GND3, Q18.2, R50.1, R51.1, U25.A1, U25.A14, U25.B5, U25.B10, U25.E2, U25.E13, U25.G7, U25.G8, U25.G14, U25.H7, U25.H8, U25.J7, U25.J8, U25.K2, U25.K6, U25.K9, U25.K13, U25.L9, U25.N1, U25.N2, U25.N5, U25.N8, U25.P1, U25.P14, U26.2, U26.17, U27.4
GND9: C262.2, C263.2, C264.2, C265.2, C266.2, C267.2, C268.2, C269.2, C270.2, C271.2, C272.2, C273.2, C274.2, C275.2, C276.2, C277.2, C278.2, C279.2, C280.2, C281.2, C282.2, C283.2, C284.2, C285.2, C286.2, C287.2, C288.2, C289.2, C290.2, D46.C, J10.1, J10.7, J10.33, J10.36, J10.39, J10.45, J10.75, J10.GND1, J10.GND2, J10.GND3, Q20.2, R56.1, R57.1, U28.A1, U28.A14, U28.B5, U28.B10, U28.E2, U28.E13, U28.G7, U28.G8, U28.G14, U28.H7, U28.H8, U28.J7, U28.J8, U28.K2, U28.K6, U28.K9, U28.K13, U28.L9, U28.N1, U28.N2, U28.N5, U28.N8, U28.P1, U28.P14, U29.2, U29.17, U30.4
GND10: C291.2, C292.2, C293.2, C294.2, C295.2, C296.2, C297.2, C298.2, C299.2, C300.2, C301.2, C302.2, C303.2, C304.2, C305.2, C306.2, C307.2, C308.2, C309.2, C310.2, C311.2, C312.2, C313.2, C314.2, C315.2, C316.2, C317.2, C318.2, C319.2, D51.C, J11.1, J11.7, J11.33, J11.36, J11.39, J11.45, J11.75, J11.GND1, J11.GND2, J11.GND3, Q22.2, R62.1, R63.1, U31.A1, U31.A14, U31.B5, U31.B10, U31.E2, U31.E13, U31.G7, U31.G8, U31.G14, U31.H7, U31.H8, U31.J7, U31.J8, U31.K2, U31.K6, U31.K9, U31.K13, U31.L9, U31.N1, U31.N2, U31.N5, U31.N8, U31.P1, U31.P14, U32.2, U32.17, U33.4
GND11: C320.2, C321.2, C322.2, C323.2, C324.2, C325.2, C326.2, C327.2, C328.2, C329.2, C330.2, C331.2, C332.2, C333.2, C334.2, C335.2, C336.2, C337.2, C338.2, C339.2, C340.2, C341.2, C342.2, C343.2, C344.2, C345.2, C346.2, C347.2, C348.2, D56.C, J12.1, J12.7, J12.33, J12.36, J12.39, J12.45, J12.75, J12.GND1, J12.GND2, J12.GND3, Q24.2, R68.1, R69.1, U34.A1, U34.A14, U34.B5, U34.B10, U34.E2, U34.E13, U34.G7, U34.G8, U34.G14, U34.H7, U34.H8, U34.J7, U34.J8, U34.K2, U34.K6, U34.K9, U34.K13, U34.L9, U34.N1, U34.N2, U34.N5, U34.N8, U34.P1, U34.P14, U35.2, U35.17, U36.4
GND12: C349.2, C350.2, C351.2, C352.2, C353.2, C354.2, C355.2, C356.2, C357.2, C358.2, C359.2, C360.2, C361.2, C362.2, C363.2, C364.2, C365.2, C366.2, C367.2, C368.2, C369.2, C370.2, C371.2, C372.2, C373.2, C374.2, C375.2, C376.2, C377.2, D61.C, J13.1, J13.7, J13.33, J13.36, J13.39, J13.45, J13.75, J13.GND1, J13.GND2, J13.GND3, Q26.2, R74.1, R75.1, U37.A1, U37.A14, U37.B5, U37.B10, U37.E2, U37.E13, U37.G7, U37.G8, U37.G14, U37.H7, U37.H8, U37.J7, U37.J8, U37.K2, U37.K6, U37.K9, U37.K13, U37.L9, U37.N1, U37.N2, U37.N5, U37.N8, U37.P1, U37.P14, U38.2, U38.17, U39.4
GND13: C378.2, C379.2, C380.2, C381.2, C382.2, C383.2, C384.2, C385.2, C386.2, C387.2, C388.2, C389.2, C390.2, C391.2, C392.2, C393.2, C394.2, C395.2, C396.2, C397.2, C398.2, C399.2, C400.2, C401.2, C402.2, C403.2, C404.2, C405.2, C406.2, D66.C, J14.1, J14.7, J14.33, J14.36, J14.39, J14.45, J14.75, J14.GND1, J14.GND2, J14.GND3, Q28.2, R80.1, R81.1, U40.A1, U40.A14, U40.B5, U40.B10, U40.E2, U40.E13, U40.G7, U40.G8, U40.G14, U40.H7, U40.H8, U40.J7, U40.J8, U40.K2, U40.K6, U40.K9, U40.K13, U40.L9, U40.N1, U40.N2, U40.N5, U40.N8, U40.P1, U40.P14, U41.2, U41.17, U42.4
GND14: C407.2, C408.2, C409.2, C410.2, C411.2, C412.2, C413.2, C414.2, C415.2, C416.2, C417.2, C418.2, C419.2, C420.2, C421.2, C422.2, C423.2, C424.2, C425.2, C426.2, C427.2, C428.2, C429.2, C430.2, C431.2, C432.2, C433.2, C434.2, C435.2, D71.C, J15.1, J15.7, J15.33, J15.36, J15.39, J15.45, J15.75, J15.GND1, J15.GND2, J15.GND3, Q30.2, R86.1, R87.1, U43.A1, U43.A14, U43.B5, U43.B10, U43.E2, U43.E13, U43.G7, U43.G8, U43.G14, U43.H7, U43.H8, U43.J7, U43.J8, U43.K2, U43.K6, U43.K9, U43.K13, U43.L9, U43.N1, U43.N2, U43.N5, U43.N8, U43.P1, U43.P14, U44.2, U44.17, U45.4
GND15: C436.2, C437.2, C438.2, C439.2, C440.2, C441.2, C442.2, C443.2, C444.2, C445.2, C446.2, C447.2, C448.2, C449.2, C450.2, C451.2, C452.2, C453.2, C454.2, C455.2, C456.2, C457.2, C458.2, C459.2, C460.2, C461.2, C462.2, C463.2, C464.2, D76.C, J16.1, J16.7, J16.33, J16.36, J16.39, J16.45, J16.75, J16.GND1, J16.GND2, J16.GND3, Q32.2, R92.1, R93.1, U46.A1, U46.A14, U46.B5, U46.B10, U46.E2, U46.E13, U46.G7, U46.G8, U46.G14, U46.H7, U46.H8, U46.J7, U46.J8, U46.K2, U46.K6, U46.K9, U46.K13, U46.L9, U46.N1, U46.N2, U46.N5, U46.N8, U46.P1, U46.P14, U47.2, U47.17, U48.4
GPIO/1: J2.69, U2.A10
GPIO/2: J2.71, U2.D9
GPIO/3: J2.65, U2.C10
GPIO/4: J2.63, U2.H4
GPIO/5: J2.40, U2.C8
GPIO/6: J1.71, U1.D9
GPIO/7: J2.42, U2.B8
GPIO/8: J2.44, U2.A8
GPIO/9: J1.69, U1.A10
GPIO/10: J2.46, U2.A9
GPIO/11: J2.48, U2.B9
GPIO/12: J2.73, U2.C9
GPIO/13: J3.69, U7.A10
GPIO/14: J3.71, U7.D9
GPIO/15: J3.65, U7.C10
GPIO/16: J3.63, U7.H4
GPIO/17: J3.40, U7.C8
GPIO/18: J3.42, U7.B8
GPIO/19: J3.44, U7.A8
GPIO/20: J3.46, U7.A9
GPIO/21: J3.48, U7.B9
GPIO/22: J3.73, U7.C9
GPIO/23: J4.69, U10.A10
GPIO/24: J4.71, U10.D9
GPIO/25: J4.65, U10.C10
GPIO/26: J4.63, U10.H4
GPIO/26/A1: J2.67, U2.G12
GPIO/26/A2: J3.67, U7.G12
GPIO/26/A3: J4.67, U10.G12
GPIO/26/A4: J5.67, U13.G12
GPIO/26/A5: J6.67, U16.G12
GPIO/26/A6: J7.67, U19.G12
GPIO/26/A7: J8.67, U22.G12
GPIO/26/A8: J9.67, U25.G12
GPIO/26/A9: J10.67, U28.G12
GPIO/26/A10: J11.67, U31.G12
GPIO/26/A11: J12.67, U34.G12
GPIO/26/A12: J1.67, U1.G12
GPIO/26/A13: J13.67, U37.G12
GPIO/26/A14: J14.67, U40.G12
GPIO/26/A15: J15.67, U43.G12
GPIO/26/A16: J16.67, U46.G12
GPIO/27: J4.40, U10.C8
GPIO/27/A1: J2.8, U2.J14
GPIO/27/A2: J3.8, U7.J14
GPIO/27/A3: J4.8, U10.J14
GPIO/27/A4: J5.8, U13.J14
GPIO/27/A5: J6.8, U16.J14
GPIO/27/A6: J7.8, U19.J14
GPIO/27/A7: J8.8, U22.J14
GPIO/27/A8: J9.8, U25.J14
GPIO/27/A9: J10.8, U28.J14
GPIO/27/A10: J11.8, U31.J14
GPIO/27/A11: J12.8, U34.J14
GPIO/27/A12: J13.8, U37.J14
GPIO/27/A13: J1.8, U1.J14
GPIO/27/A14: J14.8, U40.J14
GPIO/27/A15: J15.8, U43.J14
GPIO/27/A16: J16.8, U46.J14
GPIO/28: J4.42, U10.B8
GPIO/28/3.3V_EN: J1.4, U1.D5
GPIO/28/3.3V_EN1: J2.4, U2.D5
GPIO/28/3.3V_EN2: J3.4, U7.D5
GPIO/28/3.3V_EN3: J4.4, U10.D5
GPIO/28/3.3V_EN4: J5.4, U13.D5
GPIO/28/3.3V_EN5: J6.4, U16.D5
GPIO/28/3.3V_EN6: J7.4, U19.D5
GPIO/28/3.3V_EN7: J8.4, U22.D5
GPIO/28/3.3V_EN8: J9.4, U25.D5
GPIO/28/3.3V_EN9: J10.4, U28.D5
GPIO/28/3.3V_EN10: J11.4, U31.D5
GPIO/28/3.3V_EN11: J12.4, U34.D5
GPIO/28/3.3V_EN12: J13.4, U37.D5
GPIO/28/3.3V_EN13: J14.4, U40.D5
GPIO/28/3.3V_EN14: J15.4, U43.D5
GPIO/28/3.3V_EN15: J16.4, U46.D5
GPIO/29: J4.44, U10.A8
GPIO/30: J4.46, U10.A9
GPIO/31: J4.48, U10.B9
GPIO/32: J1.65, U1.C10
GPIO/33: J1.63, U1.H4
GPIO/34: J4.73, U10.C9
GPIO/35: J5.69, U13.A10
GPIO/36: J5.71, U13.D9
GPIO/37: J5.65, U13.C10
GPIO/38: J5.63, U13.H4
GPIO/39: J5.40, U13.C8
GPIO/40: J1.40, U1.C8
GPIO/41: J1.42, U1.B8
GPIO/42: J1.44, U1.A8
GPIO/43: J1.46, U1.A9
GPIO/44: J1.48, U1.B9
GPIO/45: J1.73, U1.C9
GPIO/46: J5.42, U13.B8
GPIO/47: J5.44, U13.A8
GPIO/48: J5.46, U13.A9
GPIO/49: J5.48, U13.B9
GPIO/50: J5.73, U13.C9
GPIO/51: J6.69, U16.A10
GPIO/52: J6.71, U16.D9
GPIO/53: J6.65, U16.C10
GPIO/54: J6.63, U16.H4
GPIO/55: J6.40, U16.C8
GPIO/56: J6.42, U16.B8
GPIO/57: J6.44, U16.A8
GPIO/58: J6.46, U16.A9
GPIO/59: J6.48, U16.B9
GPIO/60: J6.73, U16.C9
GPIO/61: J7.69, U19.A10
GPIO/62: J7.71, U19.D9
GPIO/63: J7.65, U19.C10
GPIO/64: J7.63, U19.H4
GPIO/65: J7.40, U19.C8
GPIO/66: J7.42, U19.B8
GPIO/67: J7.44, U19.A8
GPIO/68: J7.46, U19.A9
GPIO/69: J7.48, U19.B9
GPIO/70: J7.73, U19.C9
GPIO/71: J8.69, U22.A10
GPIO/72: J8.71, U22.D9
GPIO/73: J8.65, U22.C10
GPIO/74: J8.63, U22.H4
GPIO/75: J8.40, U22.C8
GPIO/76: J8.42, U22.B8
GPIO/77: J8.44, U22.A8
GPIO/78: J8.46, U22.A9
GPIO/79: J8.48, U22.B9
GPIO/80: J8.73, U22.C9
GPIO/81: J9.69, U25.A10
GPIO/82: J9.71, U25.D9
GPIO/83: J9.65, U25.C10
GPIO/84: J9.63, U25.H4
GPIO/85: J9.40, U25.C8
GPIO/86: J9.42, U25.B8
GPIO/87: J9.44, U25.A8
GPIO/88: J9.46, U25.A9
GPIO/89: J9.48, U25.B9
GPIO/90: J9.73, U25.C9
GPIO/91: J10.69, U28.A10
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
